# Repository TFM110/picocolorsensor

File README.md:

# REV Color Sensor Raspberry Pi Pico

This uses a Serial connection to transmit data for 2 Rev Color Sensors to a roboRIO using a Pi Pico.

## Pi Pico Setup

You can follow the raspberry pi instructions to build the executable in the pico folder. Their instructions are complicated for windows, so I have also provided a prebuilt uf2 file to directly upload to the device. To deploy this file this, hold down the button on your devide, and connect to your computer. This will open as a drive. Copy the picocolorsensor.uf2 file in the `pico` folder to the drive. It will automatically reboot and start running the code with no configuration required.

## Hardware connections

By default, the code will connect to 2 color sensors. 

Please solder all the necessary components onto the PCB, files are provided in the `Pico Color Sensor PCB` folder to print/order your own PCB as well as the Bill of Materials(BOM) needed for the PCB.

You may solder both the DuPont and/or the JST connector but you may only use one on both sides.

V2

Differences between V1 and V2:

* Replaced the SMDs with THTs components so teams don’t need to worry about small pieces and allows easier soldering with THTs
* Made the DuPont headers at a right angle to minimize the usage of the vertical space
* Both the Dupont and JST connector face the side
* FIXED: The JST connector on the V1 had the SDA and SCL channels in the wrong pins, V2 has fixed that. This allows you to use a regular 4-pin JST PH cable from the color sensor to the board. NOTE: When plugging the JST connector into the board, the connector must be upside down then how you plug into the color sensor.

V2.1

V2.5

Differences between V2 and V2.1/V2.5

* V2.1 and V2.5 now have 4 layers of traces instead of 2

Differences between V2.1 and V2.5

* V2.5 now has a male MXP port to allow you to use a NavX.
* V2.5 also has extra mounting holes for you to be able to securely mount the NavX
* NOTE: Due to the rule R713 in the 2022 Game Manual, you are not allowed to use any of the pins available on the NavX to control any actuators

## WPILib Setup

Copy the files corresponding to the language you use in the `wpilib` folder into your project. Instantiate a `PicoColorSensor` (java) or `pico::ColorSensor` (C++) object. You can only create 1 instance of this object. You can then use the functions to grab each color sensors value, and if its connected.

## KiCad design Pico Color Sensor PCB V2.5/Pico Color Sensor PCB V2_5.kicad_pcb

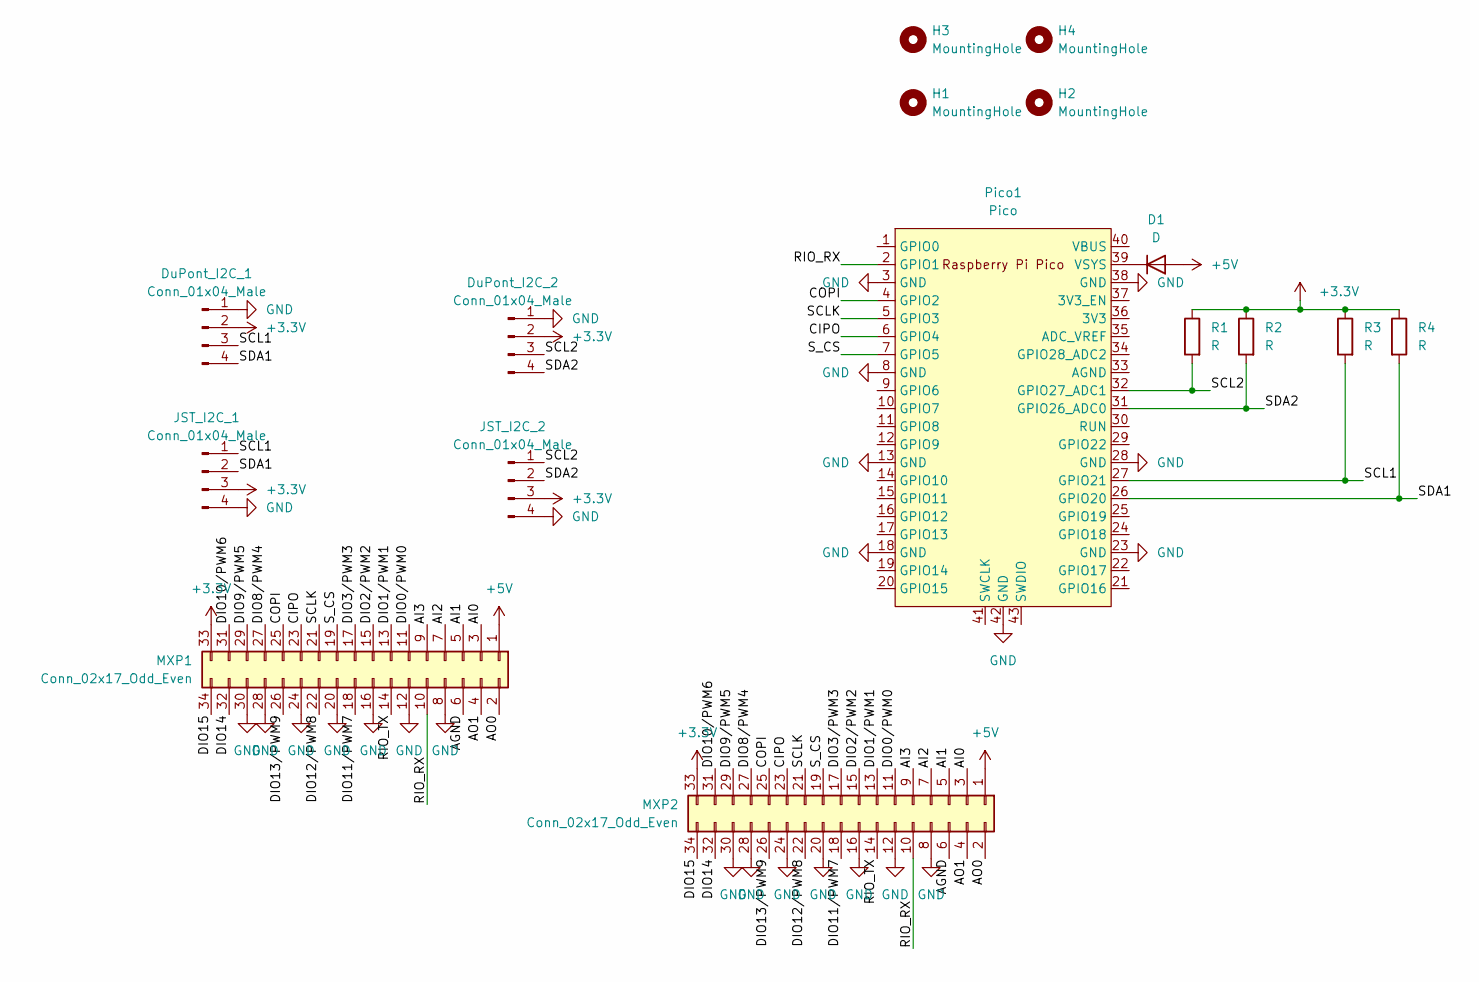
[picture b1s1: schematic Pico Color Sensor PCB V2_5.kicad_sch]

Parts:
D1: D; D_DO-15_P12.70mm_Horizontal
DuPont_I2C_1, DuPont_I2C_2: Conn_01x04_Male; PinHeader_1x04_P2.54mm_Horizontal
H1, H2, H3, H4: MountingHole; MountingHole_3.2mm_M3
JST_I2C_1, JST_I2C_2: Conn_01x04_Male; JST_PH_S4B-PH-K_1x04_P2.00mm_Horizontal
MXP1: Conn_02x17_Odd_Even; PinSocket_2x17_P2.54mm_Vertical
MXP2: Conn_02x17_Odd_Even; PinHeader_2x17_P2.54mm_Vertical
Pico1: Pico; RPi_Pico_SMD_TH
R1, R2, R3, R4: R; R_Axial_DIN0207_L6.3mm_D2.5mm_P10.16mm_Horizontal

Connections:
+3.3V: DuPont_I2C_1.2, DuPont_I2C_2.2, JST_I2C_1.3, JST_I2C_2.3, MXP1.33, MXP2.33, R1.1, R2.1, R3.1, R4.1
+5V: D1.2 (A), MXP1.1, MXP2.1
/AGND: MXP1.6, MXP2.6
/AI0: MXP1.3, MXP2.3
/AI1: MXP1.5, MXP2.5
/AI2: MXP1.7, MXP2.7
/AI3: MXP1.9, MXP2.9
/AO0: MXP1.2, MXP2.2
/AO1: MXP1.4, MXP2.4
/CIPO: MXP1.23, MXP2.23, Pico1.6 (GPIO4)
/COPI: MXP1.25, MXP2.25, Pico1.4 (GPIO2)
/DIO0/PWM0: MXP1.11, MXP2.11
/DIO1/PWM1: MXP1.13, MXP2.13
/DIO2/PWM2: MXP1.15, MXP2.15
/DIO3/PWM3: MXP1.17, MXP2.17
/DIO8/PWM4: MXP1.27, MXP2.27
/DIO9/PWM5: MXP1.29, MXP2.29
/DIO10/PWM6: MXP1.31, MXP2.31
/DIO11/PWM7: MXP1.18, MXP2.18
/DIO12/PWM8: MXP1.22, MXP2.22
/DIO13/PWM9: MXP1.26, MXP2.26
/DIO14: MXP1.32, MXP2.32
/DIO15: MXP1.34, MXP2.34
/RIO_RX: MXP1.10, MXP2.10, Pico1.2 (GPIO1)
/RIO_TX: MXP1.14, MXP2.14
/SCL1: DuPont_I2C_1.3, JST_I2C_1.1, Pico1.27 (GPIO21), R3.2
/SCL2: DuPont_I2C_2.3, JST_I2C_2.1, Pico1.32 (GPIO27_ADC1), R1.2
/SCLK: MXP1.21, MXP2.21, Pico1.5 (GPIO3)
/SDA1: DuPont_I2C_1.4, JST_I2C_1.2, Pico1.26 (GPIO20), R4.2
/SDA2: DuPont_I2C_2.4, JST_I2C_2.2, Pico1.31 (GPIO26_ADC0), R2.2
/S_CS: MXP1.19, MXP2.19, Pico1.7 (GPIO5)
GND: DuPont_I2C_1.1, DuPont_I2C_2.1, JST_I2C_1.4, JST_I2C_2.4, MXP1.8, MXP1.12, MXP1.16, MXP1.20, MXP1.24, MXP1.28, MXP1.30, MXP2.8, MXP2.12, MXP2.16, MXP2.20, MXP2.24, MXP2.28, MXP2.30, Pico1.3 (GND), Pico1.8 (GND), Pico1.13 (GND), Pico1.18 (GND), Pico1.23 (GND), Pico1.28 (GND), Pico1.38 (GND), Pico1.42 (GND)
unnamed: D1.1 (K), Pico1.39 (VSYS)

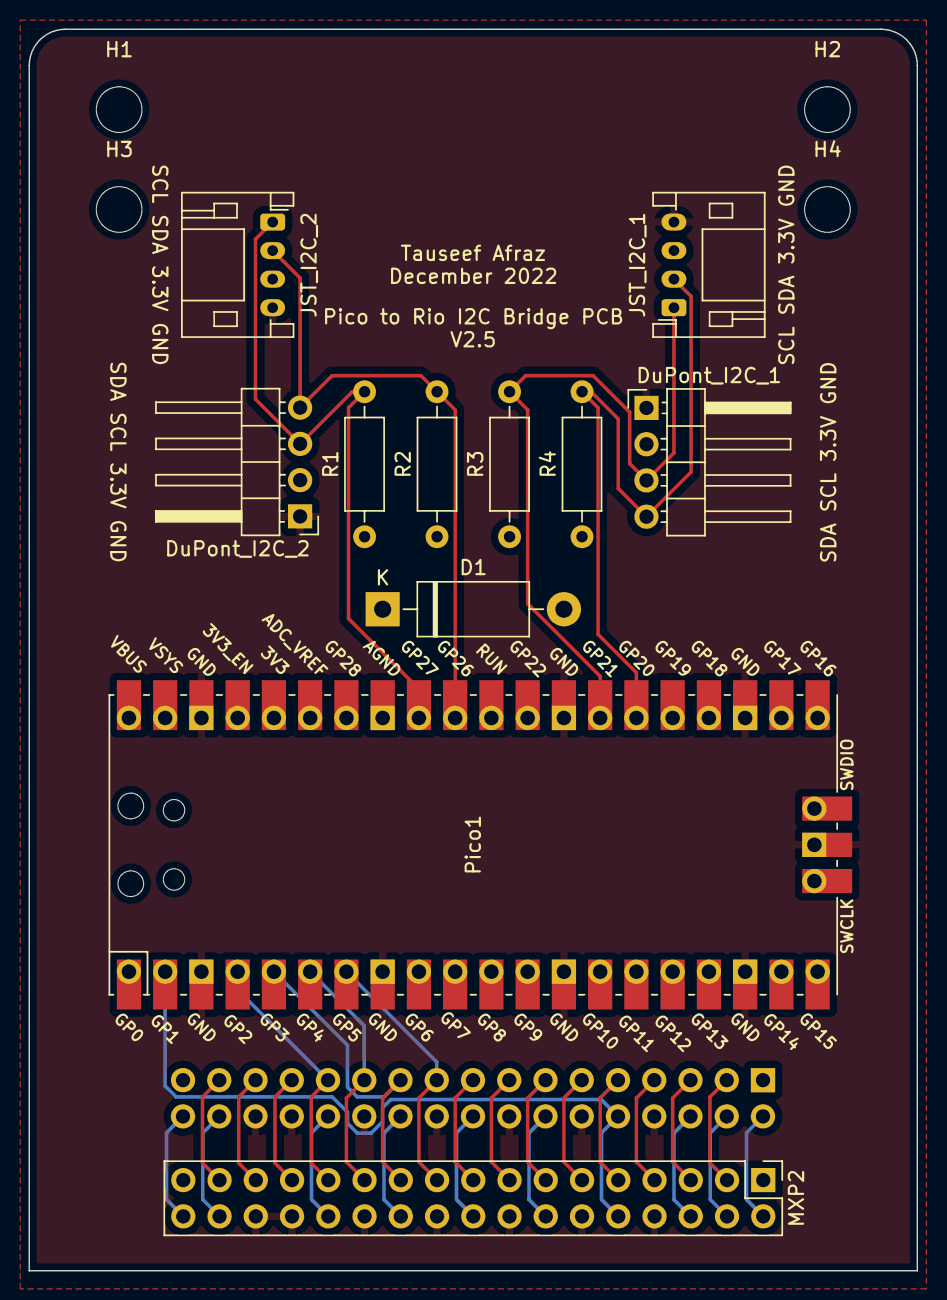
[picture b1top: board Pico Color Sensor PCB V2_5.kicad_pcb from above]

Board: 4 copper layers, 62.2 x 87.0 mm, 16 parts (1 on the bottom side), 33 nets.

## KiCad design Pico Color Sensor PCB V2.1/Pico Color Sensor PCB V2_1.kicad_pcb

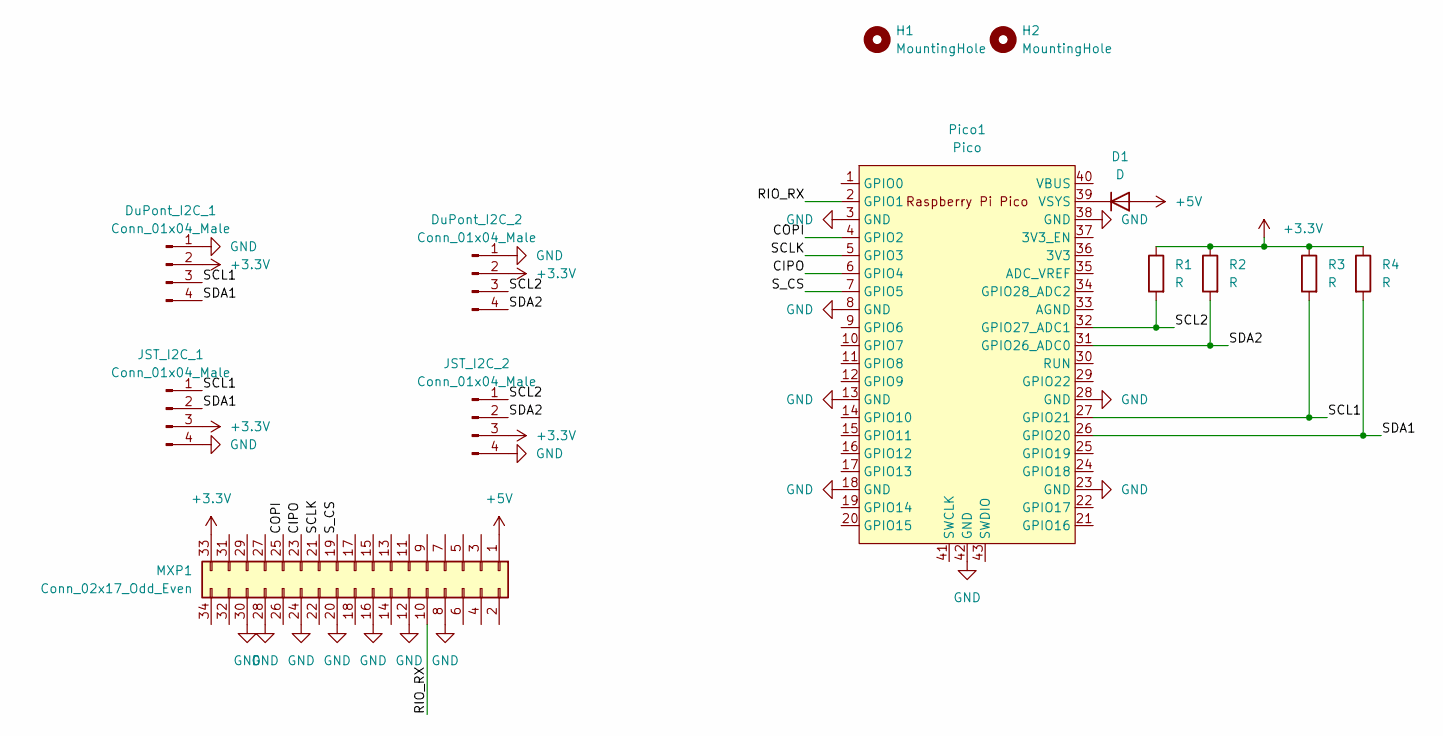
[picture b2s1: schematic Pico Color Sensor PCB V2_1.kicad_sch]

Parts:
D1: D; D_DO-15_P12.70mm_Horizontal
DuPont_I2C_1, DuPont_I2C_2: Conn_01x04_Male; PinHeader_1x04_P2.54mm_Horizontal
H1, H2: MountingHole; MountingHole_3.2mm_M3
JST_I2C_1, JST_I2C_2: Conn_01x04_Male; JST_PH_S4B-PH-K_1x04_P2.00mm_Horizontal
MXP1: Conn_02x17_Odd_Even; PinSocket_2x17_P2.54mm_Vertical
Pico1: Pico; RPi_Pico_SMD_TH
R1, R2, R3, R4: R; R_Axial_DIN0207_L6.3mm_D2.5mm_P10.16mm_Horizontal

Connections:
+3.3V: DuPont_I2C_1.2, DuPont_I2C_2.2, JST_I2C_1.3, JST_I2C_2.3, MXP1.33, R1.1, R2.1, R3.1, R4.1
+5V: D1.2 (A), MXP1.1
/CIPO: MXP1.23, Pico1.6 (GPIO4)
/COPI: MXP1.25, Pico1.4 (GPIO2)
/RIO_RX: MXP1.10, Pico1.2 (GPIO1)
/SCL1: DuPont_I2C_1.3, JST_I2C_1.1, Pico1.27 (GPIO21), R3.2
/SCL2: DuPont_I2C_2.3, JST_I2C_2.1, Pico1.32 (GPIO27_ADC1), R1.2
/SCLK: MXP1.21, Pico1.5 (GPIO3)
/SDA1: DuPont_I2C_1.4, JST_I2C_1.2, Pico1.26 (GPIO20), R4.2
/SDA2: DuPont_I2C_2.4, JST_I2C_2.2, Pico1.31 (GPIO26_ADC0), R2.2
/S_CS: MXP1.19, Pico1.7 (GPIO5)
GND: DuPont_I2C_1.1, DuPont_I2C_2.1, JST_I2C_1.4, JST_I2C_2.4, MXP1.8, MXP1.12, MXP1.16, MXP1.20, MXP1.24, MXP1.28, MXP1.30, Pico1.3 (GND), Pico1.8 (GND), Pico1.13 (GND), Pico1.18 (GND), Pico1.23 (GND), Pico1.28 (GND), Pico1.38 (GND), Pico1.42 (GND)
unnamed: D1.1 (K), Pico1.39 (VSYS)

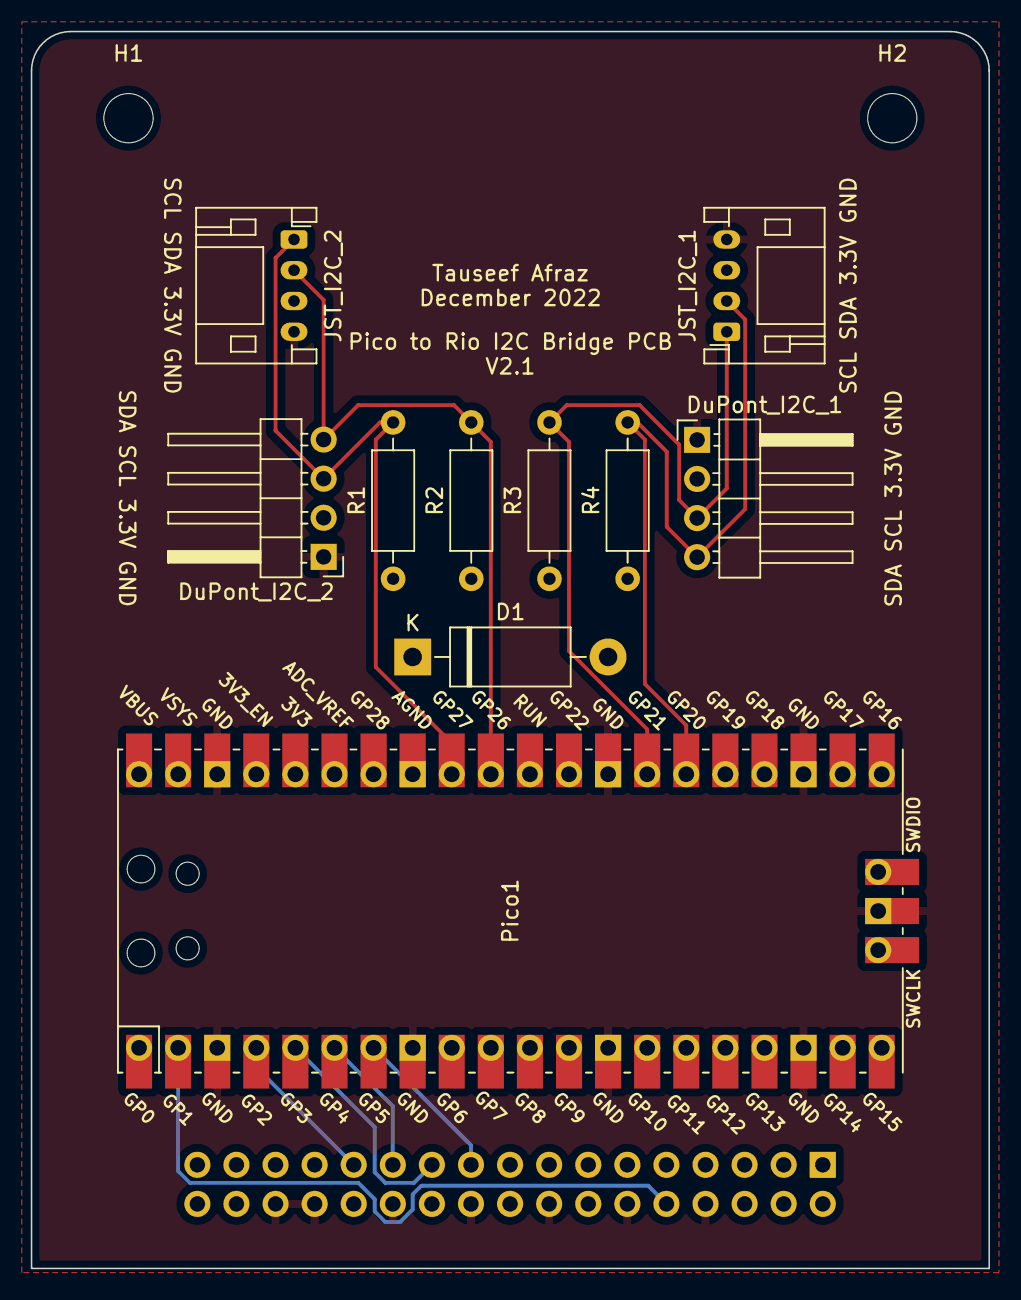
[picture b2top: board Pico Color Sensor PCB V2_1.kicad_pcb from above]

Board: 4 copper layers, 62.2 x 80.4 mm, 13 parts (1 on the bottom side), 13 nets.

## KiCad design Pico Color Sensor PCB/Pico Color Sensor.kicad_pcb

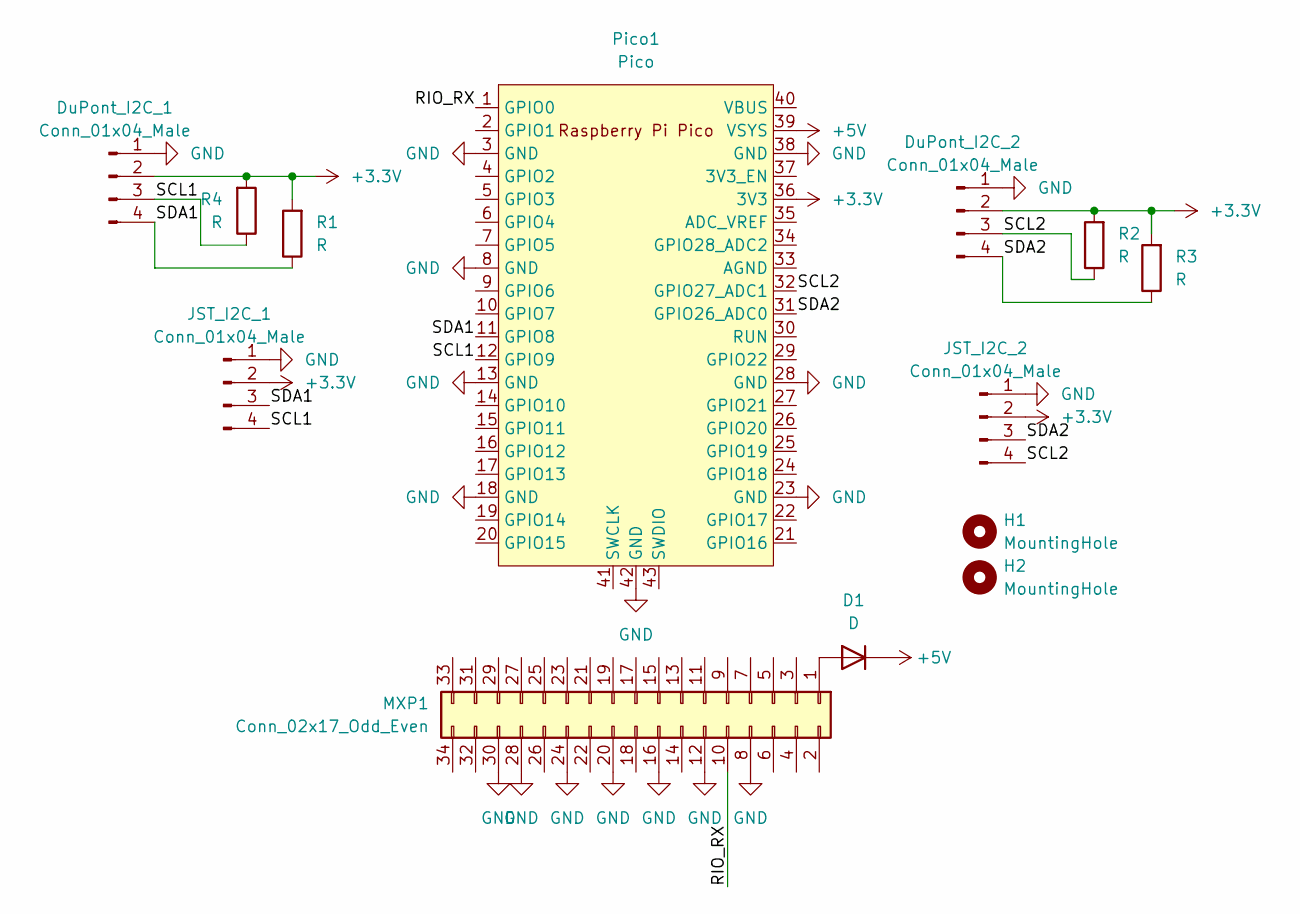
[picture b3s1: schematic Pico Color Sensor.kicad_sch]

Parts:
D1: D; D_DO-15_P10.16mm_Horizontal
DuPont_I2C_1, DuPont_I2C_2: Conn_01x04_Male; PinHeader_1x04_P2.54mm_Horizontal
H1, H2: MountingHole; MountingHole_2mm
JST_I2C_1, JST_I2C_2: Conn_01x04_Male; JST_PH_S4B-PH-K_1x04_P2.00mm_Horizontal
MXP1: Conn_02x17_Odd_Even; PinSocket_2x17_P2.54mm_Vertical
Pico1: Pico; RPi_Pico_SMD_TH
R1, R2, R3, R4: R; R_Axial_DIN0207_L6.3mm_D2.5mm_P10.16mm_Horizontal

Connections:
+3.3V: DuPont_I2C_1.2, DuPont_I2C_2.2, JST_I2C_1.2, JST_I2C_2.2, Pico1.36 (3V3), R1.2, R2.2, R3.2, R4.2
+5V: D1.1 (K), Pico1.39 (VSYS)
/RIO_RX: MXP1.10, Pico1.1 (GPIO0)
/SCL1: DuPont_I2C_1.3, JST_I2C_1.4, Pico1.12 (GPIO9), R4.1
/SCL2: DuPont_I2C_2.3, JST_I2C_2.4, Pico1.32 (GPIO27_ADC1), R2.1
/SDA1: DuPont_I2C_1.4, JST_I2C_1.3, Pico1.11 (GPIO8), R1.1
/SDA2: DuPont_I2C_2.4, JST_I2C_2.3, Pico1.31 (GPIO26_ADC0), R3.1
GND: DuPont_I2C_1.1, DuPont_I2C_2.1, JST_I2C_1.1, JST_I2C_2.1, MXP1.8, MXP1.12, MXP1.16, MXP1.20, MXP1.24, MXP1.28, MXP1.30, Pico1.3 (GND), Pico1.8 (GND), Pico1.13 (GND), Pico1.18 (GND), Pico1.23 (GND), Pico1.28 (GND), Pico1.38 (GND), Pico1.42 (GND)
unnamed: D1.2 (A), MXP1.1

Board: 2 copper layers, 13 parts (0 on the bottom side), 9 nets, no tracks yet.

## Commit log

2022-11-29 Updated IDs
2022-11-29 Added pcb files. WIP
2022-12-01 Updating PCB. Code still needs to be worked on
2022-12-01 edit gitignore
2022-12-01 Added the gerber files
2022-12-01 fingers crossed, this is the new uf2
2022-12-01 updated BOM with current prices
2022-12-01 Updated pinouts for JST
2022-12-05 Updated text
2022-12-06 Added V2 Text
2022-12-07 Added V2.1 and V2.5
2022-12-07 Made V2.5 board a bit longer
2022-12-07 Updated V2.1 and V2.5 BOM sheets title
2023-01-20 add pico files to repo
2023-04-26 i did changes i guess
